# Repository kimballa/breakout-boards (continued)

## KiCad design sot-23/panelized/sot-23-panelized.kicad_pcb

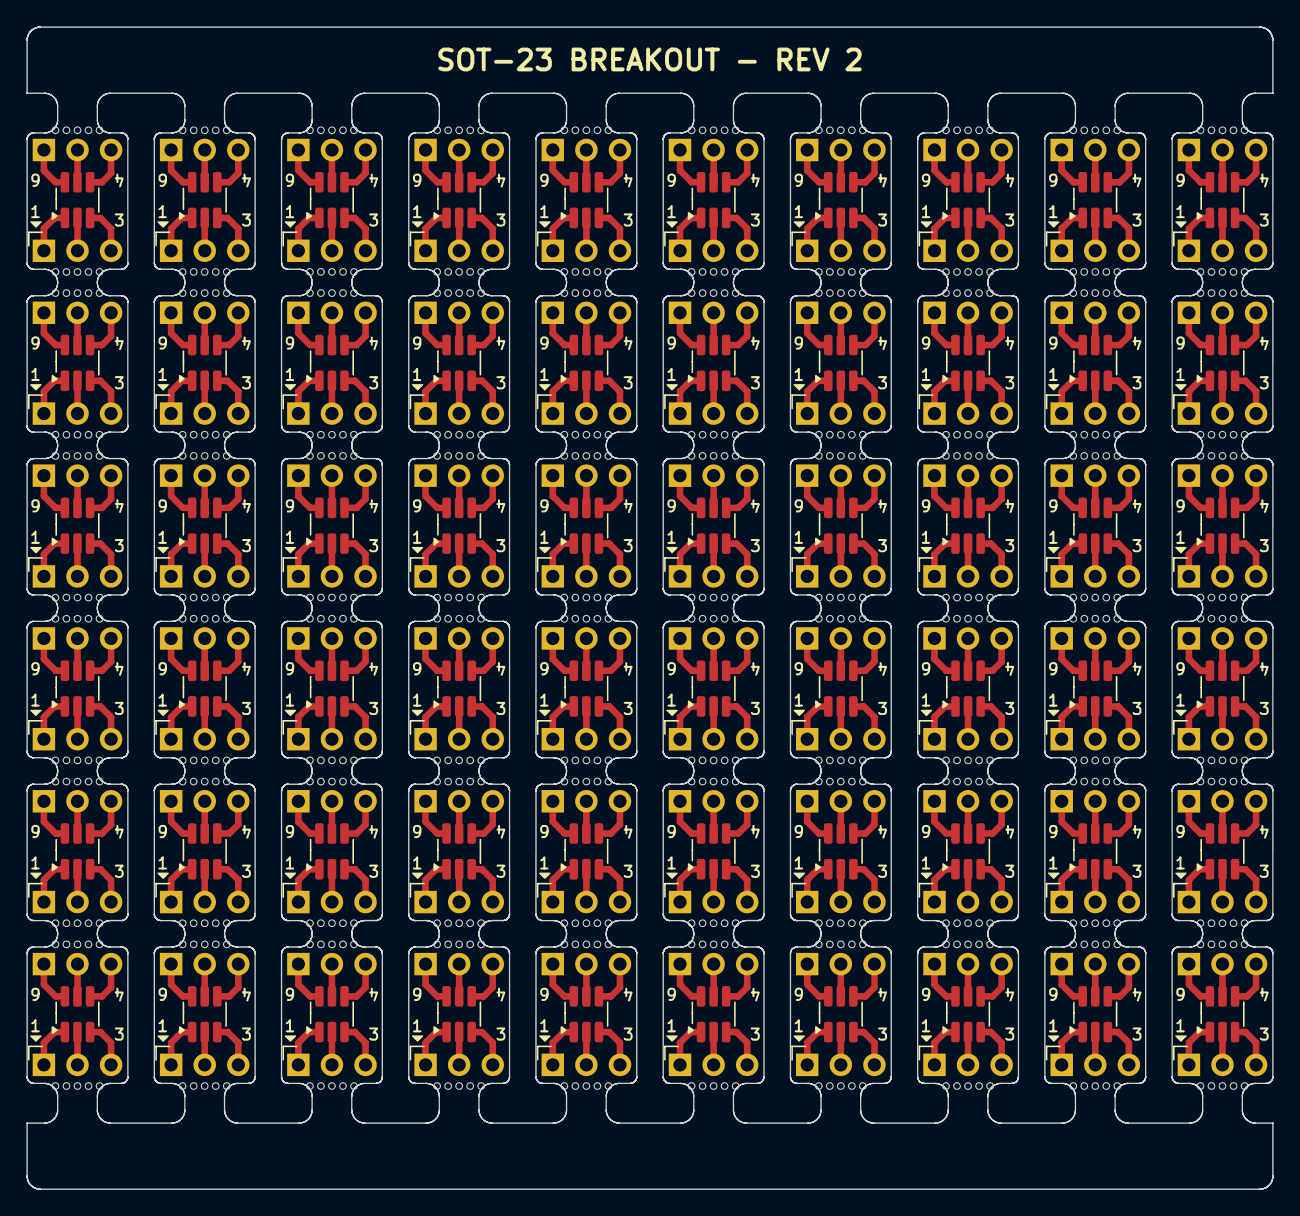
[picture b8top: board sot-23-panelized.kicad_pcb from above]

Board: 2 copper layers, 94.2 x 87.9 mm, 780 parts (0 on the bottom side), 360 nets.

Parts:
J1, J1#2, J1#3, J1#4, J1#5, J1#6, J1#7, J1#8, J1#9, J1#10, J1#11, J1#12, J1#13, J1#14, J1#15, J1#16, J1#17, J1#18, J1#19, J1#20, J1#21, J1#22, J1#23, J1#24, J1#25, J1#26, J1#27, J1#28, J1#29, J1#30, J1#31, J1#32, J1#33, J1#34, J1#35, J1#36, J1#37, J1#38, J1#39, J1#40, J1#41, J1#42, J1#43, J1#44, J1#45, J1#46, J1#47, J1#48, J1#49, J1#50, J1#51, J1#52, J1#53, J1#54, J1#55, J1#56, J1#57, J1#58, J1#59, J1#60, J2, J2#2, J2#3, J2#4, J2#5, J2#6, J2#7, J2#8, J2#9, J2#10, J2#11, J2#12, J2#13, J2#14, J2#15, J2#16, J2#17, J2#18, J2#19, J2#20, J2#21, J2#22, J2#23, J2#24, J2#25, J2#26, J2#27, J2#28, J2#29, J2#30, J2#31, J2#32, J2#33, J2#34, J2#35, J2#36, J2#37, J2#38, J2#39, J2#40, J2#41, J2#42, J2#43, J2#44, J2#45, J2#46, J2#47, J2#48, J2#49, J2#50, J2#51, J2#52, J2#53, J2#54, J2#55, J2#56, J2#57, J2#58, J2#59, J2#60: Conn_01x03; PinHeader_1x03_P2.54mm_Vertical
KiKit_MB_1_2, KiKit_MB_1_3, KiKit_MB_1_4, KiKit_MB_1_5, KiKit_MB_1_6, KiKit_MB_2_2, KiKit_MB_2_3, KiKit_MB_2_4, KiKit_MB_2_5, KiKit_MB_2_6, KiKit_MB_3_2, KiKit_MB_3_3, KiKit_MB_3_4, KiKit_MB_3_5, KiKit_MB_3_6, KiKit_MB_4_2, KiKit_MB_4_3, KiKit_MB_4_4, KiKit_MB_4_5, KiKit_MB_4_6, KiKit_MB_5_2, KiKit_MB_5_3, KiKit_MB_5_4, KiKit_MB_5_5, KiKit_MB_5_6, KiKit_MB_6_2, KiKit_MB_6_3, KiKit_MB_6_4, KiKit_MB_6_5, KiKit_MB_6_6, KiKit_MB_7_2, KiKit_MB_7_3, KiKit_MB_7_4, KiKit_MB_7_5, KiKit_MB_7_6, KiKit_MB_8_2, KiKit_MB_8_3, KiKit_MB_8_4, KiKit_MB_8_5, KiKit_MB_8_6, KiKit_MB_9_2, KiKit_MB_9_3, KiKit_MB_9_4, KiKit_MB_9_5, KiKit_MB_9_6, KiKit_MB_10_2, KiKit_MB_10_3, KiKit_MB_10_4, KiKit_MB_10_5, KiKit_MB_10_6, KiKit_MB_11_2, KiKit_MB_11_3, KiKit_MB_11_4, KiKit_MB_11_5, KiKit_MB_11_6, KiKit_MB_12_2, KiKit_MB_12_3, KiKit_MB_12_4, KiKit_MB_12_5, KiKit_MB_12_6, KiKit_MB_13_2, KiKit_MB_13_3, KiKit_MB_13_4, KiKit_MB_13_5, KiKit_MB_13_6, KiKit_MB_14_2, KiKit_MB_14_3, KiKit_MB_14_4, KiKit_MB_14_5, KiKit_MB_14_6, KiKit_MB_15_2, KiKit_MB_15_3, KiKit_MB_15_4, KiKit_MB_15_5, KiKit_MB_15_6, KiKit_MB_16_2, KiKit_MB_16_3, KiKit_MB_16_4, KiKit_MB_16_5, KiKit_MB_16_6, KiKit_MB_17_2, KiKit_MB_17_3, KiKit_MB_17_4, KiKit_MB_17_5, KiKit_MB_17_6, KiKit_MB_18_2, KiKit_MB_18_3, KiKit_MB_18_4, KiKit_MB_18_5, KiKit_MB_18_6, KiKit_MB_19_2, KiKit_MB_19_3, KiKit_MB_19_4, KiKit_MB_19_5, KiKit_MB_19_6, KiKit_MB_20_2, KiKit_MB_20_3, KiKit_MB_20_4, KiKit_MB_20_5, KiKit_MB_20_6, KiKit_MB_21_2, KiKit_MB_21_3, KiKit_MB_21_4, KiKit_MB_21_5, KiKit_MB_21_6, KiKit_MB_22_2, KiKit_MB_22_3, KiKit_MB_22_4, KiKit_MB_22_5, KiKit_MB_22_6, KiKit_MB_23_2, KiKit_MB_23_3, KiKit_MB_23_4, KiKit_MB_23_5, KiKit_MB_23_6, KiKit_MB_24_2, KiKit_MB_24_3, KiKit_MB_24_4, KiKit_MB_24_5, KiKit_MB_24_6, KiKit_MB_25_2, KiKit_MB_25_3, KiKit_MB_25_4, KiKit_MB_25_5, KiKit_MB_25_6, KiKit_MB_26_2, KiKit_MB_26_3, KiKit_MB_26_4, KiKit_MB_26_5, KiKit_MB_26_6, KiKit_MB_27_2, KiKit_MB_27_3, KiKit_MB_27_4, KiKit_MB_27_5, KiKit_MB_27_6, KiKit_MB_28_2, KiKit_MB_28_3, KiKit_MB_28_4, KiKit_MB_28_5, KiKit_MB_28_6, KiKit_MB_29_2, KiKit_MB_29_3, KiKit_MB_29_4, KiKit_MB_29_5, KiKit_MB_29_6, KiKit_MB_30_2, KiKit_MB_30_3, KiKit_MB_30_4, KiKit_MB_30_5, KiKit_MB_30_6, KiKit_MB_31_2, KiKit_MB_31_3, KiKit_MB_31_4, KiKit_MB_31_5, KiKit_MB_31_6, KiKit_MB_32_2, KiKit_MB_32_3, KiKit_MB_32_4, KiKit_MB_32_5, KiKit_MB_32_6, KiKit_MB_33_2, KiKit_MB_33_3, KiKit_MB_33_4, KiKit_MB_33_5, KiKit_MB_33_6, KiKit_MB_34_2, KiKit_MB_34_3, KiKit_MB_34_4, KiKit_MB_34_5, KiKit_MB_34_6, KiKit_MB_35_2, KiKit_MB_35_3, KiKit_MB_35_4, KiKit_MB_35_5, KiKit_MB_35_6, KiKit_MB_36_2, KiKit_MB_36_3, KiKit_MB_36_4, KiKit_MB_36_5, KiKit_MB_36_6, KiKit_MB_37_2, KiKit_MB_37_3, KiKit_MB_37_4, KiKit_MB_37_5, KiKit_MB_37_6, KiKit_MB_38_2, KiKit_MB_38_3, KiKit_MB_38_4, KiKit_MB_38_5, KiKit_MB_38_6, KiKit_MB_39_2, KiKit_MB_39_3, KiKit_MB_39_4, KiKit_MB_39_5, KiKit_MB_39_6, KiKit_MB_40_2, KiKit_MB_40_3, KiKit_MB_40_4, KiKit_MB_40_5, KiKit_MB_40_6, KiKit_MB_41_2, KiKit_MB_41_3, KiKit_MB_41_4, KiKit_MB_41_5, KiKit_MB_41_6, KiKit_MB_42_2, KiKit_MB_42_3, KiKit_MB_42_4, KiKit_MB_42_5, KiKit_MB_42_6, KiKit_MB_43_2, KiKit_MB_43_3, KiKit_MB_43_4, KiKit_MB_43_5, KiKit_MB_43_6, KiKit_MB_44_2, KiKit_MB_44_3, KiKit_MB_44_4, KiKit_MB_44_5, KiKit_MB_44_6, KiKit_MB_45_2, KiKit_MB_45_3, KiKit_MB_45_4, KiKit_MB_45_5, KiKit_MB_45_6, KiKit_MB_46_2, KiKit_MB_46_3, KiKit_MB_46_4, KiKit_MB_46_5, KiKit_MB_46_6, KiKit_MB_47_2, KiKit_MB_47_3, KiKit_MB_47_4, KiKit_MB_47_5, KiKit_MB_47_6, KiKit_MB_48_2, KiKit_MB_48_3, KiKit_MB_48_4, KiKit_MB_48_5, KiKit_MB_48_6, KiKit_MB_49_2, KiKit_MB_49_3, KiKit_MB_49_4, KiKit_MB_49_5, KiKit_MB_49_6, KiKit_MB_50_2, KiKit_MB_50_3, KiKit_MB_50_4, KiKit_MB_50_5, KiKit_MB_50_6, KiKit_MB_51_2, KiKit_MB_51_3, KiKit_MB_51_4, KiKit_MB_51_5, KiKit_MB_51_6, KiKit_MB_52_2, KiKit_MB_52_3, KiKit_MB_52_4, KiKit_MB_52_5, KiKit_MB_52_6, KiKit_MB_53_2, KiKit_MB_53_3, KiKit_MB_53_4, KiKit_MB_53_5, KiKit_MB_53_6, KiKit_MB_54_2, KiKit_MB_54_3, KiKit_MB_54_4, KiKit_MB_54_5, KiKit_MB_54_6, KiKit_MB_55_2, KiKit_MB_55_3, KiKit_MB_55_4, KiKit_MB_55_5, KiKit_MB_55_6, KiKit_MB_56_2, KiKit_MB_56_3, KiKit_MB_56_4, KiKit_MB_56_5, KiKit_MB_56_6, KiKit_MB_57_2, KiKit_MB_57_3, KiKit_MB_57_4, KiKit_MB_57_5, KiKit_MB_57_6, KiKit_MB_58_2, KiKit_MB_58_3, KiKit_MB_58_4, KiKit_MB_58_5, KiKit_MB_58_6, KiKit_MB_59_2, KiKit_MB_59_3, KiKit_MB_59_4, KiKit_MB_59_5, KiKit_MB_59_6, KiKit_MB_60_2, KiKit_MB_60_3, KiKit_MB_60_4, KiKit_MB_60_5, KiKit_MB_60_6, KiKit_MB_61_2, KiKit_MB_61_3, KiKit_MB_61_4, KiKit_MB_61_5, KiKit_MB_61_6, KiKit_MB_62_2, KiKit_MB_62_3, KiKit_MB_62_4, KiKit_MB_62_5, KiKit_MB_62_6, KiKit_MB_63_2, KiKit_MB_63_3, KiKit_MB_63_4, KiKit_MB_63_5, KiKit_MB_63_6, KiKit_MB_64_2, KiKit_MB_64_3, KiKit_MB_64_4, KiKit_MB_64_5, KiKit_MB_64_6, KiKit_MB_65_2, KiKit_MB_65_3, KiKit_MB_65_4, KiKit_MB_65_5, KiKit_MB_65_6, KiKit_MB_66_2, KiKit_MB_66_3, KiKit_MB_66_4, KiKit_MB_66_5, KiKit_MB_66_6, KiKit_MB_67_2, KiKit_MB_67_3, KiKit_MB_67_4, KiKit_MB_67_5, KiKit_MB_67_6, KiKit_MB_68_2, KiKit_MB_68_3, KiKit_MB_68_4, KiKit_MB_68_5, KiKit_MB_68_6, KiKit_MB_69_2, KiKit_MB_69_3, KiKit_MB_69_4, KiKit_MB_69_5, KiKit_MB_69_6, KiKit_MB_70_2, KiKit_MB_70_3, KiKit_MB_70_4, KiKit_MB_70_5, KiKit_MB_70_6, KiKit_MB_71_2, KiKit_MB_71_3, KiKit_MB_71_4, KiKit_MB_71_5, KiKit_MB_71_6, KiKit_MB_72_2, KiKit_MB_72_3, KiKit_MB_72_4, KiKit_MB_72_5, KiKit_MB_72_6, KiKit_MB_73_2, KiKit_MB_73_3, KiKit_MB_73_4, KiKit_MB_73_5, KiKit_MB_73_6, KiKit_MB_74_2, KiKit_MB_74_3, KiKit_MB_74_4, KiKit_MB_74_5, KiKit_MB_74_6, KiKit_MB_75_2, KiKit_MB_75_3, KiKit_MB_75_4, KiKit_MB_75_5, KiKit_MB_75_6, KiKit_MB_76_2, KiKit_MB_76_3, KiKit_MB_76_4, KiKit_MB_76_5, KiKit_MB_76_6, KiKit_MB_77_2, KiKit_MB_77_3, KiKit_MB_77_4, KiKit_MB_77_5, KiKit_MB_77_6, KiKit_MB_78_2, KiKit_MB_78_3, KiKit_MB_78_4, KiKit_MB_78_5, KiKit_MB_78_6, KiKit_MB_79_2, KiKit_MB_79_3, KiKit_MB_79_4, KiKit_MB_79_5, KiKit_MB_79_6, KiKit_MB_80_2, KiKit_MB_80_3, KiKit_MB_80_4, KiKit_MB_80_5, KiKit_MB_80_6, KiKit_MB_81_2, KiKit_MB_81_3, KiKit_MB_81_4, KiKit_MB_81_5, KiKit_MB_81_6, KiKit_MB_82_2, KiKit_MB_82_3, KiKit_MB_82_4, KiKit_MB_82_5, KiKit_MB_82_6, KiKit_MB_83_2, KiKit_MB_83_3, KiKit_MB_83_4, KiKit_MB_83_5, KiKit_MB_83_6, KiKit_MB_84_2, KiKit_MB_84_3, KiKit_MB_84_4, KiKit_MB_84_5, KiKit_MB_84_6, KiKit_MB_85_2, KiKit_MB_85_3, KiKit_MB_85_4, KiKit_MB_85_5, KiKit_MB_85_6, KiKit_MB_86_2, KiKit_MB_86_3, KiKit_MB_86_4, KiKit_MB_86_5, KiKit_MB_86_6, KiKit_MB_87_2, KiKit_MB_87_3, KiKit_MB_87_4, KiKit_MB_87_5, KiKit_MB_87_6, KiKit_MB_88_2, KiKit_MB_88_3, KiKit_MB_88_4, KiKit_MB_88_5, KiKit_MB_88_6, KiKit_MB_89_2, KiKit_MB_89_3, KiKit_MB_89_4, KiKit_MB_89_5, KiKit_MB_89_6, KiKit_MB_90_2, KiKit_MB_90_3, KiKit_MB_90_4, KiKit_MB_90_5, KiKit_MB_90_6, KiKit_MB_91_2, KiKit_MB_91_3, KiKit_MB_91_4, KiKit_MB_91_5, KiKit_MB_91_6, KiKit_MB_92_2, KiKit_MB_92_3, KiKit_MB_92_4, KiKit_MB_92_5, KiKit_MB_92_6, KiKit_MB_93_2, KiKit_MB_93_3, KiKit_MB_93_4, KiKit_MB_93_5, KiKit_MB_93_6, KiKit_MB_94_2, KiKit_MB_94_3, KiKit_MB_94_4, KiKit_MB_94_5, KiKit_MB_94_6, KiKit_MB_95_2, KiKit_MB_95_3, KiKit_MB_95_4, KiKit_MB_95_5, KiKit_MB_95_6, KiKit_MB_96_2, KiKit_MB_96_3, KiKit_MB_96_4, KiKit_MB_96_5, KiKit_MB_96_6, KiKit_MB_97_2, KiKit_MB_97_3, KiKit_MB_97_4, KiKit_MB_97_5, KiKit_MB_97_6, KiKit_MB_98_2, KiKit_MB_98_3, KiKit_MB_98_4, KiKit_MB_98_5, KiKit_MB_98_6, KiKit_MB_99_2, KiKit_MB_99_3, KiKit_MB_99_4, KiKit_MB_99_5, KiKit_MB_99_6, KiKit_MB_100_2, KiKit_MB_100_3, KiKit_MB_100_4, KiKit_MB_100_5, KiKit_MB_100_6, KiKit_MB_101_2, KiKit_MB_101_3, KiKit_MB_101_4, KiKit_MB_101_5, KiKit_MB_101_6, KiKit_MB_102_2, KiKit_MB_102_3, KiKit_MB_102_4, KiKit_MB_102_5, KiKit_MB_102_6, KiKit_MB_103_2, KiKit_MB_103_3, KiKit_MB_103_4, KiKit_MB_103_5, KiKit_MB_103_6, KiKit_MB_104_2, KiKit_MB_104_3, KiKit_MB_104_4, KiKit_MB_104_5, KiKit_MB_104_6, KiKit_MB_105_2, KiKit_MB_105_3, KiKit_MB_105_4, KiKit_MB_105_5, KiKit_MB_105_6, KiKit_MB_106_2, KiKit_MB_106_3, KiKit_MB_106_4, KiKit_MB_106_5, KiKit_MB_106_6, KiKit_MB_107_2, KiKit_MB_107_3, KiKit_MB_107_4, KiKit_MB_107_5, KiKit_MB_107_6, KiKit_MB_108_2, KiKit_MB_108_3, KiKit_MB_108_4, KiKit_MB_108_5, KiKit_MB_108_6, KiKit_MB_109_2, KiKit_MB_109_3, KiKit_MB_109_4, KiKit_MB_109_5, KiKit_MB_109_6, KiKit_MB_110_2, KiKit_MB_110_3, KiKit_MB_110_4, KiKit_MB_110_5, KiKit_MB_110_6, KiKit_MB_111_2, KiKit_MB_111_3, KiKit_MB_111_4, KiKit_MB_111_5, KiKit_MB_111_6, KiKit_MB_112_2, KiKit_MB_112_3, KiKit_MB_112_4, KiKit_MB_112_5, KiKit_MB_112_6, KiKit_MB_113_2, KiKit_MB_113_3, KiKit_MB_113_4, KiKit_MB_113_5, KiKit_MB_113_6, KiKit_MB_114_2, KiKit_MB_114_3, KiKit_MB_114_4, KiKit_MB_114_5, KiKit_MB_114_6, KiKit_MB_115_2, KiKit_MB_115_3, KiKit_MB_115_4, KiKit_MB_115_5, KiKit_MB_115_6, KiKit_MB_116_2, KiKit_MB_116_3, KiKit_MB_116_4, KiKit_MB_116_5, KiKit_MB_116_6, KiKit_MB_117_2, KiKit_MB_117_3, KiKit_MB_117_4, KiKit_MB_117_5, KiKit_MB_117_6, KiKit_MB_118_2, KiKit_MB_118_3, KiKit_MB_118_4, KiKit_MB_118_5, KiKit_MB_118_6, KiKit_MB_119_2, KiKit_MB_119_3, KiKit_MB_119_4, KiKit_MB_119_5, KiKit_MB_119_6, KiKit_MB_120_2, KiKit_MB_120_3, KiKit_MB_120_4, KiKit_MB_120_5, KiKit_MB_120_6: NPTH
Q1, Q1#2, Q1#3, Q1#4, Q1#5, Q1#6, Q1#7, Q1#8, Q1#9, Q1#10, Q1#11, Q1#12, Q1#13, Q1#14, Q1#15, Q1#16, Q1#17, Q1#18, Q1#19, Q1#20, Q1#21, Q1#22, Q1#23, Q1#24, Q1#25, Q1#26, Q1#27, Q1#28, Q1#29, Q1#30, Q1#31, Q1#32, Q1#33, Q1#34, Q1#35, Q1#36, Q1#37, Q1#38, Q1#39, Q1#40, Q1#41, Q1#42, Q1#43, Q1#44, Q1#45, Q1#46, Q1#47, Q1#48, Q1#49, Q1#50, Q1#51, Q1#52, Q1#53, Q1#54, Q1#55, Q1#56, Q1#57, Q1#58, Q1#59, Q1#60: BCM847DS; SOT-23-6_Handsoldering

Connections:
Board_0-Net-(J1-Pin_1): J1#17.1, Q1#11.1 (E1)
Board_0-Net-(J1-Pin_2): J1#17.2, Q1#11.2 (B1)
Board_0-Net-(J1-Pin_3): J1#17.3, Q1#11.3 (C2)
Board_0-Net-(J2-Pin_1): J2#59.1, Q1#11.6 (C1)
Board_0-Net-(J2-Pin_2): J2#59.2, Q1#11.5 (B2)
Board_0-Net-(J2-Pin_3): J2#59.3, Q1#11.4 (E2)
Board_1-Net-(J1-Pin_1): J1#7.1, Q1#18.1 (E1)
Board_1-Net-(J1-Pin_2): J1#7.2, Q1#18.2 (B1)
Board_1-Net-(J1-Pin_3): J1#7.3, Q1#18.3 (C2)
Board_1-Net-(J2-Pin_1): J2#15.1, Q1#18.6 (C1)
Board_1-Net-(J2-Pin_2): J2#15.2, Q1#18.5 (B2)
Board_1-Net-(J2-Pin_3): J2#15.3, Q1#18.4 (E2)
Board_2-Net-(J1-Pin_1): J1#5.1, Q1#51.1 (E1)
Board_2-Net-(J1-Pin_2): J1#5.2, Q1#51.2 (B1)
Board_2-Net-(J1-Pin_3): J1#5.3, Q1#51.3 (C2)
Board_2-Net-(J2-Pin_1): J2#28.1, Q1#51.6 (C1)
Board_2-Net-(J2-Pin_2): J2#28.2, Q1#51.5 (B2)
Board_2-Net-(J2-Pin_3): J2#28.3, Q1#51.4 (E2)
Board_3-Net-(J1-Pin_1): J1#29.1, Q1#7.1 (E1)
Board_3-Net-(J1-Pin_2): J1#29.2, Q1#7.2 (B1)
Board_3-Net-(J1-Pin_3): J1#29.3, Q1#7.3 (C2)
Board_3-Net-(J2-Pin_1): J2#50.1, Q1#7.6 (C1)
Board_3-Net-(J2-Pin_2): J2#50.2, Q1#7.5 (B2)
Board_3-Net-(J2-Pin_3): J2#50.3, Q1#7.4 (E2)
Board_4-Net-(J1-Pin_1): J1#21.1, Q1.1 (E1)
Board_4-Net-(J1-Pin_2): J1#21.2, Q1.2 (B1)
Board_4-Net-(J1-Pin_3): J1#21.3, Q1.3 (C2)
Board_4-Net-(J2-Pin_1): J2#4.1, Q1.6 (C1)
Board_4-Net-(J2-Pin_2): J2#4.2, Q1.5 (B2)
Board_4-Net-(J2-Pin_3): J2#4.3, Q1.4 (E2)
Board_5-Net-(J1-Pin_1): J1#3.1, Q1#6.1 (E1)
Board_5-Net-(J1-Pin_2): J1#3.2, Q1#6.2 (B1)
Board_5-Net-(J1-Pin_3): J1#3.3, Q1#6.3 (C2)
Board_5-Net-(J2-Pin_1): J2#33.1, Q1#6.6 (C1)
Board_5-Net-(J2-Pin_2): J2#33.2, Q1#6.5 (B2)
Board_5-Net-(J2-Pin_3): J2#33.3, Q1#6.4 (E2)
Board_6-Net-(J1-Pin_1): J1#14.1, Q1#57.1 (E1)
Board_6-Net-(J1-Pin_2): J1#14.2, Q1#57.2 (B1)
Board_6-Net-(J1-Pin_3): J1#14.3, Q1#57.3 (C2)
Board_6-Net-(J2-Pin_1): J2#31.1, Q1#57.6 (C1)
Board_6-Net-(J2-Pin_2): J2#31.2, Q1#57.5 (B2)
Board_6-Net-(J2-Pin_3): J2#31.3, Q1#57.4 (E2)
Board_7-Net-(J1-Pin_1): J1#37.1, Q1#50.1 (E1)
Board_7-Net-(J1-Pin_2): J1#37.2, Q1#50.2 (B1)
Board_7-Net-(J1-Pin_3): J1#37.3, Q1#50.3 (C2)
Board_7-Net-(J2-Pin_1): J2#44.1, Q1#50.6 (C1)
Board_7-Net-(J2-Pin_2): J2#44.2, Q1#50.5 (B2)
Board_7-Net-(J2-Pin_3): J2#44.3, Q1#50.4 (E2)
Board_8-Net-(J1-Pin_1): J1#26.1, Q1#58.1 (E1)
Board_8-Net-(J1-Pin_2): J1#26.2, Q1#58.2 (B1)
Board_8-Net-(J1-Pin_3): J1#26.3, Q1#58.3 (C2)
Board_8-Net-(J2-Pin_1): J2#22.1, Q1#58.6 (C1)
Board_8-Net-(J2-Pin_2): J2#22.2, Q1#58.5 (B2)
Board_8-Net-(J2-Pin_3): J2#22.3, Q1#58.4 (E2)
Board_9-Net-(J1-Pin_1): J1#22.1, Q1#53.1 (E1)
Board_9-Net-(J1-Pin_2): J1#22.2, Q1#53.2 (B1)
Board_9-Net-(J1-Pin_3): J1#22.3, Q1#53.3 (C2)
Board_9-Net-(J2-Pin_1): J2#12.1, Q1#53.6 (C1)
Board_9-Net-(J2-Pin_2): J2#12.2, Q1#53.5 (B2)
Board_9-Net-(J2-Pin_3): J2#12.3, Q1#53.4 (E2)
Board_10-Net-(J1-Pin_1): J1#2.1, Q1#5.1 (E1)
Board_10-Net-(J1-Pin_2): J1#2.2, Q1#5.2 (B1)
Board_10-Net-(J1-Pin_3): J1#2.3, Q1#5.3 (C2)
Board_10-Net-(J2-Pin_1): J2#48.1, Q1#5.6 (C1)
Board_10-Net-(J2-Pin_2): J2#48.2, Q1#5.5 (B2)
Board_10-Net-(J2-Pin_3): J2#48.3, Q1#5.4 (E2)
Board_11-Net-(J1-Pin_1): J1#35.1, Q1#28.1 (E1)
Board_11-Net-(J1-Pin_2): J1#35.2, Q1#28.2 (B1)
Board_11-Net-(J1-Pin_3): J1#35.3, Q1#28.3 (C2)
Board_11-Net-(J2-Pin_1): J2#23.1, Q1#28.6 (C1)
Board_11-Net-(J2-Pin_2): J2#23.2, Q1#28.5 (B2)
Board_11-Net-(J2-Pin_3): J2#23.3, Q1#28.4 (E2)
Board_12-Net-(J1-Pin_1): J1#32.1, Q1#33.1 (E1)
Board_12-Net-(J1-Pin_2): J1#32.2, Q1#33.2 (B1)
Board_12-Net-(J1-Pin_3): J1#32.3, Q1#33.3 (C2)
Board_12-Net-(J2-Pin_1): J2#19.1, Q1#33.6 (C1)
Board_12-Net-(J2-Pin_2): J2#19.2, Q1#33.5 (B2)
Board_12-Net-(J2-Pin_3): J2#19.3, Q1#33.4 (E2)
Board_13-Net-(J1-Pin_1): J1#56.1, Q1#9.1 (E1)
Board_13-Net-(J1-Pin_2): J1#56.2, Q1#9.2 (B1)
Board_13-Net-(J1-Pin_3): J1#56.3, Q1#9.3 (C2)
Board_13-Net-(J2-Pin_1): J2#17.1, Q1#9.6 (C1)
Board_13-Net-(J2-Pin_2): J2#17.2, Q1#9.5 (B2)
Board_13-Net-(J2-Pin_3): J2#17.3, Q1#9.4 (E2)
Board_14-Net-(J1-Pin_1): J1#16.1, Q1#42.1 (E1)
Board_14-Net-(J1-Pin_2): J1#16.2, Q1#42.2 (B1)
Board_14-Net-(J1-Pin_3): J1#16.3, Q1#42.3 (C2)
Board_14-Net-(J2-Pin_1): J2#57.1, Q1#42.6 (C1)
Board_14-Net-(J2-Pin_2): J2#57.2, Q1#42.5 (B2)
Board_14-Net-(J2-Pin_3): J2#57.3, Q1#42.4 (E2)
Board_15-Net-(J1-Pin_1): J1#43.1, Q1#26.1 (E1)
Board_15-Net-(J1-Pin_2): J1#43.2, Q1#26.2 (B1)
Board_15-Net-(J1-Pin_3): J1#43.3, Q1#26.3 (C2)
Board_15-Net-(J2-Pin_1): J2#35.1, Q1#26.6 (C1)
Board_15-Net-(J2-Pin_2): J2#35.2, Q1#26.5 (B2)
Board_15-Net-(J2-Pin_3): J2#35.3, Q1#26.4 (E2)
Board_16-Net-(J1-Pin_1): J1#41.1, Q1#4.1 (E1)
Board_16-Net-(J1-Pin_2): J1#41.2, Q1#4.2 (B1)
Board_16-Net-(J1-Pin_3): J1#41.3, Q1#4.3 (C2)
Board_16-Net-(J2-Pin_1): J2#2.1, Q1#4.6 (C1)
Board_16-Net-(J2-Pin_2): J2#2.2, Q1#4.5 (B2)
Board_16-Net-(J2-Pin_3): J2#2.3, Q1#4.4 (E2)
Board_17-Net-(J1-Pin_1): J1#40.1, Q1#25.1 (E1)
Board_17-Net-(J1-Pin_2): J1#40.2, Q1#25.2 (B1)
Board_17-Net-(J1-Pin_3): J1#40.3, Q1#25.3 (C2)
Board_17-Net-(J2-Pin_1): J2.1, Q1#25.6 (C1)
Board_17-Net-(J2-Pin_2): J2.2, Q1#25.5 (B2)
Board_17-Net-(J2-Pin_3): J2.3, Q1#25.4 (E2)
Board_18-Net-(J1-Pin_1): J1#50.1, Q1#14.1 (E1)
Board_18-Net-(J1-Pin_2): J1#50.2, Q1#14.2 (B1)
Board_18-Net-(J1-Pin_3): J1#50.3, Q1#14.3 (C2)
Board_18-Net-(J2-Pin_1): J2#13.1, Q1#14.6 (C1)
Board_18-Net-(J2-Pin_2): J2#13.2, Q1#14.5 (B2)
Board_18-Net-(J2-Pin_3): J2#13.3, Q1#14.4 (E2)
Board_19-Net-(J1-Pin_1): J1#49.1, Q1#54.1 (E1)
Board_19-Net-(J1-Pin_2): J1#49.2, Q1#54.2 (B1)
Board_19-Net-(J1-Pin_3): J1#49.3, Q1#54.3 (C2)
Board_19-Net-(J2-Pin_1): J2#34.1, Q1#54.6 (C1)
Board_19-Net-(J2-Pin_2): J2#34.2, Q1#54.5 (B2)
Board_19-Net-(J2-Pin_3): J2#34.3, Q1#54.4 (E2)
Board_20-Net-(J1-Pin_1): J1#46.1, Q1#30.1 (E1)
Board_20-Net-(J1-Pin_2): J1#46.2, Q1#30.2 (B1)
Board_20-Net-(J1-Pin_3): J1#46.3, Q1#30.3 (C2)
Board_20-Net-(J2-Pin_1): J2#60.1, Q1#30.6 (C1)
Board_20-Net-(J2-Pin_2): J2#60.2, Q1#30.5 (B2)
Board_20-Net-(J2-Pin_3): J2#60.3, Q1#30.4 (E2)
Board_21-Net-(J1-Pin_1): J1#48.1, Q1#60.1 (E1)
Board_21-Net-(J1-Pin_2): J1#48.2, Q1#60.2 (B1)
Board_21-Net-(J1-Pin_3): J1#48.3, Q1#60.3 (C2)
Board_21-Net-(J2-Pin_1): J2#40.1, Q1#60.6 (C1)
Board_21-Net-(J2-Pin_2): J2#40.2, Q1#60.5 (B2)
Board_21-Net-(J2-Pin_3): J2#40.3, Q1#60.4 (E2)
Board_22-Net-(J1-Pin_1): J1#58.1, Q1#49.1 (E1)
Board_22-Net-(J1-Pin_2): J1#58.2, Q1#49.2 (B1)
Board_22-Net-(J1-Pin_3): J1#58.3, Q1#49.3 (C2)
Board_22-Net-(J2-Pin_1): J2#10.1, Q1#49.6 (C1)
Board_22-Net-(J2-Pin_2): J2#10.2, Q1#49.5 (B2)
Board_22-Net-(J2-Pin_3): J2#10.3, Q1#49.4 (E2)
Board_23-Net-(J1-Pin_1): J1#15.1, Q1#44.1 (E1)
Board_23-Net-(J1-Pin_2): J1#15.2, Q1#44.2 (B1)
Board_23-Net-(J1-Pin_3): J1#15.3, Q1#44.3 (C2)
Board_23-Net-(J2-Pin_1): J2#7.1, Q1#44.6 (C1)
Board_23-Net-(J2-Pin_2): J2#7.2, Q1#44.5 (B2)
Board_23-Net-(J2-Pin_3): J2#7.3, Q1#44.4 (E2)
Board_24-Net-(J1-Pin_1): J1#20.1, Q1#23.1 (E1)
Board_24-Net-(J1-Pin_2): J1#20.2, Q1#23.2 (B1)
Board_24-Net-(J1-Pin_3): J1#20.3, Q1#23.3 (C2)
Board_24-Net-(J2-Pin_1): J2#24.1, Q1#23.6 (C1)
Board_24-Net-(J2-Pin_2): J2#24.2, Q1#23.5 (B2)
Board_24-Net-(J2-Pin_3): J2#24.3, Q1#23.4 (E2)
Board_25-Net-(J1-Pin_1): J1#19.1, Q1#22.1 (E1)
Board_25-Net-(J1-Pin_2): J1#19.2, Q1#22.2 (B1)
Board_25-Net-(J1-Pin_3): J1#19.3, Q1#22.3 (C2)
Board_25-Net-(J2-Pin_1): J2#39.1, Q1#22.6 (C1)
Board_25-Net-(J2-Pin_2): J2#39.2, Q1#22.5 (B2)
Board_25-Net-(J2-Pin_3): J2#39.3, Q1#22.4 (E2)
Board_26-Net-(J1-Pin_1): J1#31.1, Q1#56.1 (E1)
Board_26-Net-(J1-Pin_2): J1#31.2, Q1#56.2 (B1)
Board_26-Net-(J1-Pin_3): J1#31.3, Q1#56.3 (C2)
Board_26-Net-(J2-Pin_1): J2#58.1, Q1#56.6 (C1)
Board_26-Net-(J2-Pin_2): J2#58.2, Q1#56.5 (B2)
Board_26-Net-(J2-Pin_3): J2#58.3, Q1#56.4 (E2)
Board_27-Net-(J1-Pin_1): J1#33.1, Q1#40.1 (E1)
Board_27-Net-(J1-Pin_2): J1#33.2, Q1#40.2 (B1)
Board_27-Net-(J1-Pin_3): J1#33.3, Q1#40.3 (C2)
Board_27-Net-(J2-Pin_1): J2#49.1, Q1#40.6 (C1)
Board_27-Net-(J2-Pin_2): J2#49.2, Q1#40.5 (B2)
Board_27-Net-(J2-Pin_3): J2#49.3, Q1#40.4 (E2)
Board_28-Net-(J1-Pin_1): J1#30.1, Q1#19.1 (E1)
Board_28-Net-(J1-Pin_2): J1#30.2, Q1#19.2 (B1)
Board_28-Net-(J1-Pin_3): J1#30.3, Q1#19.3 (C2)
Board_28-Net-(J2-Pin_1): J2#42.1, Q1#19.6 (C1)
Board_28-Net-(J2-Pin_2): J2#42.2, Q1#19.5 (B2)
Board_28-Net-(J2-Pin_3): J2#42.3, Q1#19.4 (E2)
Board_29-Net-(J1-Pin_1): J1#18.1, Q1#24.1 (E1)
Board_29-Net-(J1-Pin_2): J1#18.2, Q1#24.2 (B1)
Board_29-Net-(J1-Pin_3): J1#18.3, Q1#24.3 (C2)
Board_29-Net-(J2-Pin_1): J2#5.1, Q1#24.6 (C1)
Board_29-Net-(J2-Pin_2): J2#5.2, Q1#24.5 (B2)
Board_29-Net-(J2-Pin_3): J2#5.3, Q1#24.4 (E2)
Board_30-Net-(J1-Pin_1): J1#57.1, Q1#35.1 (E1)
Board_30-Net-(J1-Pin_2): J1#57.2, Q1#35.2 (B1)
Board_30-Net-(J1-Pin_3): J1#57.3, Q1#35.3 (C2)
Board_30-Net-(J2-Pin_1): J2#53.1, Q1#35.6 (C1)
Board_30-Net-(J2-Pin_2): J2#53.2, Q1#35.5 (B2)
Board_30-Net-(J2-Pin_3): J2#53.3, Q1#35.4 (E2)
Board_31-Net-(J1-Pin_1): J1#52.1, Q1#55.1 (E1)
Board_31-Net-(J1-Pin_2): J1#52.2, Q1#55.2 (B1)
Board_31-Net-(J1-Pin_3): J1#52.3, Q1#55.3 (C2)
Board_31-Net-(J2-Pin_1): J2#41.1, Q1#55.6 (C1)
Board_31-Net-(J2-Pin_2): J2#41.2, Q1#55.5 (B2)
Board_31-Net-(J2-Pin_3): J2#41.3, Q1#55.4 (E2)
Board_32-Net-(J1-Pin_1): J1#11.1, Q1#3.1 (E1)
Board_32-Net-(J1-Pin_2): J1#11.2, Q1#3.2 (B1)
Board_32-Net-(J1-Pin_3): J1#11.3, Q1#3.3 (C2)
Board_32-Net-(J2-Pin_1): J2#46.1, Q1#3.6 (C1)
Board_32-Net-(J2-Pin_2): J2#46.2, Q1#3.5 (B2)
Board_32-Net-(J2-Pin_3): J2#46.3, Q1#3.4 (E2)
Board_33-Net-(J1-Pin_1): J1#13.1, Q1#27.1 (E1)
Board_33-Net-(J1-Pin_2): J1#13.2, Q1#27.2 (B1)
Board_33-Net-(J1-Pin_3): J1#13.3, Q1#27.3 (C2)
Board_33-Net-(J2-Pin_1): J2#51.1, Q1#27.6 (C1)
Board_33-Net-(J2-Pin_2): J2#51.2, Q1#27.5 (B2)
Board_33-Net-(J2-Pin_3): J2#51.3, Q1#27.4 (E2)
Board_34-Net-(J1-Pin_1): J1#25.1, Q1#34.1 (E1)
Board_34-Net-(J1-Pin_2): J1#25.2, Q1#34.2 (B1)
Board_34-Net-(J1-Pin_3): J1#25.3, Q1#34.3 (C2)
Board_34-Net-(J2-Pin_1): J2#47.1, Q1#34.6 (C1)
Board_34-Net-(J2-Pin_2): J2#47.2, Q1#34.5 (B2)
Board_34-Net-(J2-Pin_3): J2#47.3, Q1#34.4 (E2)
Board_35-Net-(J1-Pin_1): J1#4.1, Q1#20.1 (E1)
Board_35-Net-(J1-Pin_2): J1#4.2, Q1#20.2 (B1)
Board_35-Net-(J1-Pin_3): J1#4.3, Q1#20.3 (C2)
Board_35-Net-(J2-Pin_1): J2#27.1, Q1#20.6 (C1)
Board_35-Net-(J2-Pin_2): J2#27.2, Q1#20.5 (B2)
Board_35-Net-(J2-Pin_3): J2#27.3, Q1#20.4 (E2)
Board_36-Net-(J1-Pin_1): J1#39.1, Q1#37.1 (E1)
Board_36-Net-(J1-Pin_2): J1#39.2, Q1#37.2 (B1)
Board_36-Net-(J1-Pin_3): J1#39.3, Q1#37.3 (C2)
Board_36-Net-(J2-Pin_1): J2#6.1, Q1#37.6 (C1)
Board_36-Net-(J2-Pin_2): J2#6.2, Q1#37.5 (B2)
Board_36-Net-(J2-Pin_3): J2#6.3, Q1#37.4 (E2)
Board_37-Net-(J1-Pin_1): J1#42.1, Q1#32.1 (E1)
Board_37-Net-(J1-Pin_2): J1#42.2, Q1#32.2 (B1)
Board_37-Net-(J1-Pin_3): J1#42.3, Q1#32.3 (C2)
Board_37-Net-(J2-Pin_1): J2#11.1, Q1#32.6 (C1)
Board_37-Net-(J2-Pin_2): J2#11.2, Q1#32.5 (B2)
Board_37-Net-(J2-Pin_3): J2#11.3, Q1#32.4 (E2)
Board_38-Net-(J1-Pin_1): J1#51.1, Q1#43.1 (E1)
Board_38-Net-(J1-Pin_2): J1#51.2, Q1#43.2 (B1)
Board_38-Net-(J1-Pin_3): J1#51.3, Q1#43.3 (C2)
Board_38-Net-(J2-Pin_1): J2#45.1, Q1#43.6 (C1)
Board_38-Net-(J2-Pin_2): J2#45.2, Q1#43.5 (B2)
Board_38-Net-(J2-Pin_3): J2#45.3, Q1#43.4 (E2)
Board_39-Net-(J1-Pin_1): J1#24.1, Q1#48.1 (E1)
Board_39-Net-(J1-Pin_2): J1#24.2, Q1#48.2 (B1)
Board_39-Net-(J1-Pin_3): J1#24.3, Q1#48.3 (C2)
Board_39-Net-(J2-Pin_1): J2#16.1, Q1#48.6 (C1)
Board_39-Net-(J2-Pin_2): J2#16.2, Q1#48.5 (B2)
Board_39-Net-(J2-Pin_3): J2#16.3, Q1#48.4 (E2)
Board_40-Net-(J1-Pin_1): J1#44.1, Q1#16.1 (E1)
Board_40-Net-(J1-Pin_2): J1#44.2, Q1#16.2 (B1)
Board_40-Net-(J1-Pin_3): J1#44.3, Q1#16.3 (C2)
Board_40-Net-(J2-Pin_1): J2#3.1, Q1#16.6 (C1)
Board_40-Net-(J2-Pin_2): J2#3.2, Q1#16.5 (B2)
Board_40-Net-(J2-Pin_3): J2#3.3, Q1#16.4 (E2)
Board_41-Net-(J1-Pin_1): J1#6.1, Q1#13.1 (E1)
Board_41-Net-(J1-Pin_2): J1#6.2, Q1#13.2 (B1)
Board_41-Net-(J1-Pin_3): J1#6.3, Q1#13.3 (C2)
Board_41-Net-(J2-Pin_1): J2#14.1, Q1#13.6 (C1)
Board_41-Net-(J2-Pin_2): J2#14.2, Q1#13.5 (B2)
Board_41-Net-(J2-Pin_3): J2#14.3, Q1#13.4 (E2)
Board_42-Net-(J1-Pin_1): J1#8.1, Q1#46.1 (E1)
Board_42-Net-(J1-Pin_2): J1#8.2, Q1#46.2 (B1)
Board_42-Net-(J1-Pin_3): J1#8.3, Q1#46.3 (C2)
Board_42-Net-(J2-Pin_1): J2#18.1, Q1#46.6 (C1)
Board_42-Net-(J2-Pin_2): J2#18.2, Q1#46.5 (B2)
Board_42-Net-(J2-Pin_3): J2#18.3, Q1#46.4 (E2)
Board_43-Net-(J1-Pin_1): J1#9.1, Q1#38.1 (E1)
Board_43-Net-(J1-Pin_2): J1#9.2, Q1#38.2 (B1)
Board_43-Net-(J1-Pin_3): J1#9.3, Q1#38.3 (C2)
Board_43-Net-(J2-Pin_1): J2#20.1, Q1#38.6 (C1)
Board_43-Net-(J2-Pin_2): J2#20.2, Q1#38.5 (B2)
Board_43-Net-(J2-Pin_3): J2#20.3, Q1#38.4 (E2)
Board_44-Net-(J1-Pin_1): J1#27.1, Q1#29.1 (E1)
Board_44-Net-(J1-Pin_2): J1#27.2, Q1#29.2 (B1)
Board_44-Net-(J1-Pin_3): J1#27.3, Q1#29.3 (C2)
Board_44-Net-(J2-Pin_1): J2#43.1, Q1#29.6 (C1)
Board_44-Net-(J2-Pin_2): J2#43.2, Q1#29.5 (B2)
Board_44-Net-(J2-Pin_3): J2#43.3, Q1#29.4 (E2)
Board_45-Net-(J1-Pin_1): J1.1, Q1#39.1 (E1)
Board_45-Net-(J1-Pin_2): J1.2, Q1#39.2 (B1)
Board_45-Net-(J1-Pin_3): J1.3, Q1#39.3 (C2)
Board_45-Net-(J2-Pin_1): J2#8.1, Q1#39.6 (C1)
Board_45-Net-(J2-Pin_2): J2#8.2, Q1#39.5 (B2)
Board_45-Net-(J2-Pin_3): J2#8.3, Q1#39.4 (E2)
Board_46-Net-(J1-Pin_1): J1#60.1, Q1#15.1 (E1)
Board_46-Net-(J1-Pin_2): J1#60.2, Q1#15.2 (B1)
Board_46-Net-(J1-Pin_3): J1#60.3, Q1#15.3 (C2)
Board_46-Net-(J2-Pin_1): J2#21.1, Q1#15.6 (C1)
Board_46-Net-(J2-Pin_2): J2#21.2, Q1#15.5 (B2)
Board_46-Net-(J2-Pin_3): J2#21.3, Q1#15.4 (E2)
Board_47-Net-(J1-Pin_1): J1#12.1, Q1#52.1 (E1)
Board_47-Net-(J1-Pin_2): J1#12.2, Q1#52.2 (B1)
Board_47-Net-(J1-Pin_3): J1#12.3, Q1#52.3 (C2)
Board_47-Net-(J2-Pin_1): J2#26.1, Q1#52.6 (C1)
Board_47-Net-(J2-Pin_2): J2#26.2, Q1#52.5 (B2)
Board_47-Net-(J2-Pin_3): J2#26.3, Q1#52.4 (E2)
Board_48-Net-(J1-Pin_1): J1#36.1, Q1#59.1 (E1)
Board_48-Net-(J1-Pin_2): J1#36.2, Q1#59.2 (B1)
Board_48-Net-(J1-Pin_3): J1#36.3, Q1#59.3 (C2)
Board_48-Net-(J2-Pin_1): J2#30.1, Q1#59.6 (C1)
Board_48-Net-(J2-Pin_2): J2#30.2, Q1#59.5 (B2)
Board_48-Net-(J2-Pin_3): J2#30.3, Q1#59.4 (E2)
Board_49-Net-(J1-Pin_1): J1#34.1, Q1#2.1 (E1)
Board_49-Net-(J1-Pin_2): J1#34.2, Q1#2.2 (B1)
Board_49-Net-(J1-Pin_3): J1#34.3, Q1#2.3 (C2)
Board_49-Net-(J2-Pin_1): J2#36.1, Q1#2.6 (C1)
Board_49-Net-(J2-Pin_2): J2#36.2, Q1#2.5 (B2)
Board_49-Net-(J2-Pin_3): J2#36.3, Q1#2.4 (E2)
Board_50-Net-(J1-Pin_1): J1#53.1, Q1#31.1 (E1)
Board_50-Net-(J1-Pin_2): J1#53.2, Q1#31.2 (B1)
Board_50-Net-(J1-Pin_3): J1#53.3, Q1#31.3 (C2)
Board_50-Net-(J2-Pin_1): J2#9.1, Q1#31.6 (C1)
Board_50-Net-(J2-Pin_2): J2#9.2, Q1#31.5 (B2)
Board_50-Net-(J2-Pin_3): J2#9.3, Q1#31.4 (E2)
Board_51-Net-(J1-Pin_1): J1#23.1, Q1#21.1 (E1)
Board_51-Net-(J1-Pin_2): J1#23.2, Q1#21.2 (B1)
Board_51-Net-(J1-Pin_3): J1#23.3, Q1#21.3 (C2)
Board_51-Net-(J2-Pin_1): J2#54.1, Q1#21.6 (C1)
Board_51-Net-(J2-Pin_2): J2#54.2, Q1#21.5 (B2)
Board_51-Net-(J2-Pin_3): J2#54.3, Q1#21.4 (E2)
Board_52-Net-(J1-Pin_1): J1#55.1, Q1#12.1 (E1)
Board_52-Net-(J1-Pin_2): J1#55.2, Q1#12.2 (B1)
Board_52-Net-(J1-Pin_3): J1#55.3, Q1#12.3 (C2)
Board_52-Net-(J2-Pin_1): J2#52.1, Q1#12.6 (C1)
Board_52-Net-(J2-Pin_2): J2#52.2, Q1#12.5 (B2)
Board_52-Net-(J2-Pin_3): J2#52.3, Q1#12.4 (E2)
Board_53-Net-(J1-Pin_1): J1#54.1, Q1#47.1 (E1)
Board_53-Net-(J1-Pin_2): J1#54.2, Q1#47.2 (B1)
Board_53-Net-(J1-Pin_3): J1#54.3, Q1#47.3 (C2)
Board_53-Net-(J2-Pin_1): J2#56.1, Q1#47.6 (C1)
Board_53-Net-(J2-Pin_2): J2#56.2, Q1#47.5 (B2)
Board_53-Net-(J2-Pin_3): J2#56.3, Q1#47.4 (E2)
Board_54-Net-(J1-Pin_1): J1#38.1, Q1#45.1 (E1)
Board_54-Net-(J1-Pin_2): J1#38.2, Q1#45.2 (B1)
Board_54-Net-(J1-Pin_3): J1#38.3, Q1#45.3 (C2)
Board_54-Net-(J2-Pin_1): J2#37.1, Q1#45.6 (C1)
Board_54-Net-(J2-Pin_2): J2#37.2, Q1#45.5 (B2)
Board_54-Net-(J2-Pin_3): J2#37.3, Q1#45.4 (E2)
Board_55-Net-(J1-Pin_1): J1#28.1, Q1#41.1 (E1)
Board_55-Net-(J1-Pin_2): J1#28.2, Q1#41.2 (B1)
Board_55-Net-(J1-Pin_3): J1#28.3, Q1#41.3 (C2)
Board_55-Net-(J2-Pin_1): J2#38.1, Q1#41.6 (C1)
Board_55-Net-(J2-Pin_2): J2#38.2, Q1#41.5 (B2)
Board_55-Net-(J2-Pin_3): J2#38.3, Q1#41.4 (E2)
Board_56-Net-(J1-Pin_1): J1#45.1, Q1#8.1 (E1)
Board_56-Net-(J1-Pin_2): J1#45.2, Q1#8.2 (B1)
Board_56-Net-(J1-Pin_3): J1#45.3, Q1#8.3 (C2)
Board_56-Net-(J2-Pin_1): J2#25.1, Q1#8.6 (C1)
Board_56-Net-(J2-Pin_2): J2#25.2, Q1#8.5 (B2)
Board_56-Net-(J2-Pin_3): J2#25.3, Q1#8.4 (E2)
Board_57-Net-(J1-Pin_1): J1#59.1, Q1#10.1 (E1)
Board_57-Net-(J1-Pin_2): J1#59.2, Q1#10.2 (B1)
Board_57-Net-(J1-Pin_3): J1#59.3, Q1#10.3 (C2)
Board_57-Net-(J2-Pin_1): J2#32.1, Q1#10.6 (C1)
Board_57-Net-(J2-Pin_2): J2#32.2, Q1#10.5 (B2)
Board_57-Net-(J2-Pin_3): J2#32.3, Q1#10.4 (E2)
Board_58-Net-(J1-Pin_1): J1#10.1, Q1#17.1 (E1)
Board_58-Net-(J1-Pin_2): J1#10.2, Q1#17.2 (B1)
Board_58-Net-(J1-Pin_3): J1#10.3, Q1#17.3 (C2)
Board_58-Net-(J2-Pin_1): J2#55.1, Q1#17.6 (C1)
Board_58-Net-(J2-Pin_2): J2#55.2, Q1#17.5 (B2)
Board_58-Net-(J2-Pin_3): J2#55.3, Q1#17.4 (E2)
Board_59-Net-(J1-Pin_1): J1#47.1, Q1#36.1 (E1)
Board_59-Net-(J1-Pin_2): J1#47.2, Q1#36.2 (B1)
Board_59-Net-(J1-Pin_3): J1#47.3, Q1#36.3 (C2)
Board_59-Net-(J2-Pin_1): J2#29.1, Q1#36.6 (C1)
Board_59-Net-(J2-Pin_2): J2#29.2, Q1#36.5 (B2)
Board_59-Net-(J2-Pin_3): J2#29.3, Q1#36.4 (E2)

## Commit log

2026-02-18 Add top-level files.
2026-02-18 Add SOIC.
2026-02-18 Add SOT-23.
2026-02-18 Add SOIC-DW
2026-02-18 Add QFN-20 and micromatch-20.
2026-02-18 Update ordering instructions.
2026-02-18 Add SOIC-DW RTM v1 gerbers.
2026-02-18 Add QFN-20 RTM gerbers.
2026-02-21 clarify width in readme.
2026-05-08 Add SO-8-FET footprint panel.
